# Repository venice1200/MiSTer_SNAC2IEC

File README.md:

# MiSTer_SNAC2IEC
Inspired from the [SNAC Accessory Converter](https://github.com/blue212/SNAC) and the IEC Support of the C64 Core  
I created together with dtimber this little Adapter PCB for the MiSTer FPGA.  
  
The Adapter converts the MiSTer FPGA User Port (Serial IO) into a Commodore IEC/CBM (Serial) Bus Port.    
Use the Adapter to connect a real Commodore Floppy 1541 or compatible devices (SD2IEC/PI1541) to your MiSTer.  
  
I know there are better and faster ways to load a game into a MiSTer's Core, but this is fun 🚀.  
  
### Compatible & Tested Cores  
C64, C128, Commodore Plus/4  
### Tested Hardware  
[SD2IEC](https://www.c64-wiki.com/wiki/SD2IEC), [PI1541](https://cbm-pi1541.firebaseapp.com/), CBM 1541, CBM1541-II, CBM1571, CBM1581 and Printer MPS-803.
  
Cores and some Hardware Devices are also tested with **JiffyDOS** 🚀.  
  
Double check the User Video below.   
  
### Let's go and have fun...
I used "breakout Parts" for the used Voltage-Levelshifter and the Voltage-Regulator as I had them in stock.  
There is also a Full-SMD-Version available, created by dtimber who created the Case as well.  
  
## PCB's
### First Versions  
### Breakout v1.1/SMD v1.0
The first Picture shows the "Breakout Version", the second the "Full-SMD Version".  

### Updated Version(s)  
### Breakout v1.2/SMD 1.1  
Changes:
  * Added support for the SRQ Signal which is needed by the C128 Core for **Fast Serial Mode**.  
    The Breakout Version v1.2 need a second Leveshifter **on Top** of the first one to support the SRQ Signal.  
    Solder two small cables from the Pins LV5 and HV5 to one channel of the second Levelshifter.  
  * Removed 5V support (R1-R4) which needs a Standard SNAC Adapter connected before SNAC2IEC.  
  
The first Picture shows the "Breakout Version", the second the "Full-SMD Version".  

## More Pictures
The Case was designed to look like the C64 Power Supply  

Connector View  
  
Left Connector = IEC/CBM Bus, right Connector = 5V Power from SNAC Port  
                                                     
Soldered PCB Version **with** Level Shifter.  
Use it with the Standard IO Board with SNAC Port and **3.3V** Signal Level.  
  
You need all parts except the "optional's".
  
Soldered PCB Version **without** Level Shifter.  
Only usable with the "first" PCB Versions.  
Use it with SNAC Port's with integrated Level Shifter or with blue212's external SNAC Adapter and **5V** Signal Level.  
  
Just add some 0R 0805 Resistors or a blob of solder to R1,R2,R3 and R4.  

A look inside...  

All Parts for the Breakout-Version  

### BOM Breakout Version  
|Part|Type|
|:---|:---|
|R1-R4|0 ohm 0805 resistors (optional, see schematics)|
|C1|4,7uF 0805 capacitor (optional, see schematics)|
|J1|USB3 type A connector|
|J2|6 pin DIN connector (MAS60)|
|J3|DC barrel connector (optional, 5.5/2.1 mm should be fine for most PSUs)|  
|U1|4-Channel Voltage-Levelshifter (5V/3.3V), add a second ***stacked*** Levelshifter for SRQ|
|U2|5V to 3.3V Voltage Regulator|
  
### BOM Full-SMD-Version v1.0 
|Part|Type|
|:---|:---|
|R1-R4|0 ohm 0805 resistors (optional, see schematics)|
|R5-R12|10k 0805 resistors|
|C1-C3|22nf 0805 capacitors|
|Q1-Q4|N-Channel SOT23 MOSFET transistors (BSS138 or similar)|
|U1|3.3v LM1117 SOT223 regulator|
|J1|USB3 type A connector|
|J2|6 pin DIN connector (MAS60)|
|J3|DC barrel connector (optional, 5.5/2.1 mm should be fine for most PSUs)|  
  
### BOM Full-SMD-Version v1.1 
|Part|Type|
|:---|:---|
|R1-R10|10k 0805 resistors|
|C1-C3|22nf 0805 capacitors|
|Q1-Q5|N-Channel SOT23 MOSFET transistors (BSS138 or similar)|
|U1|3.3v LM1117 SOT223 regulator|
|J1|USB3 type A connector|
|J2|6 pin DIN connector (MAS60)|
|J3|DC barrel connector (optional, 5.5/2.1 mm should be fine for most PSUs)|  
  
### Screws and Brass Nuts  
|Part|Type|
|:---|:---|
|Brass Nuts|M3, outer size 4,6mm, lenght 6mm|
|Screws|M3, Counter Sunk, length 17mm|

### Many Thanks to:
*  [dtimber](https://github.com/dtimber) was helping me with KiCad and he is the Creator of the Case and the **SMD-Version**.
  
### Links:  
*  https://github.com/MiSTer-devel/Main_MiSTer/wiki  
*  https://github.com/MiSTer-devel/Main_MiSTer/wiki/User-Port-(Serial-IO)  
*  https://github.com/MiSTer-devel/C64_MiSTer
*  https://github.com/blue212/SNAC
*  https://misterfpga.org/
*  https://misterfpga.org/viewtopic.php?t=4469
  
### User-Videos:  
* https://youtu.be/zR52L662JqI
* https://www.youtube.com/watch?v=zR52L662JqI
* https://www.youtube.com/watch?v=jKdF6Q4ZU_g
* https://www.youtube.com/watch?v=Q-g8Mt_xXnU
* https://www.youtube.com/watch?v=LXGE7Ap88mE

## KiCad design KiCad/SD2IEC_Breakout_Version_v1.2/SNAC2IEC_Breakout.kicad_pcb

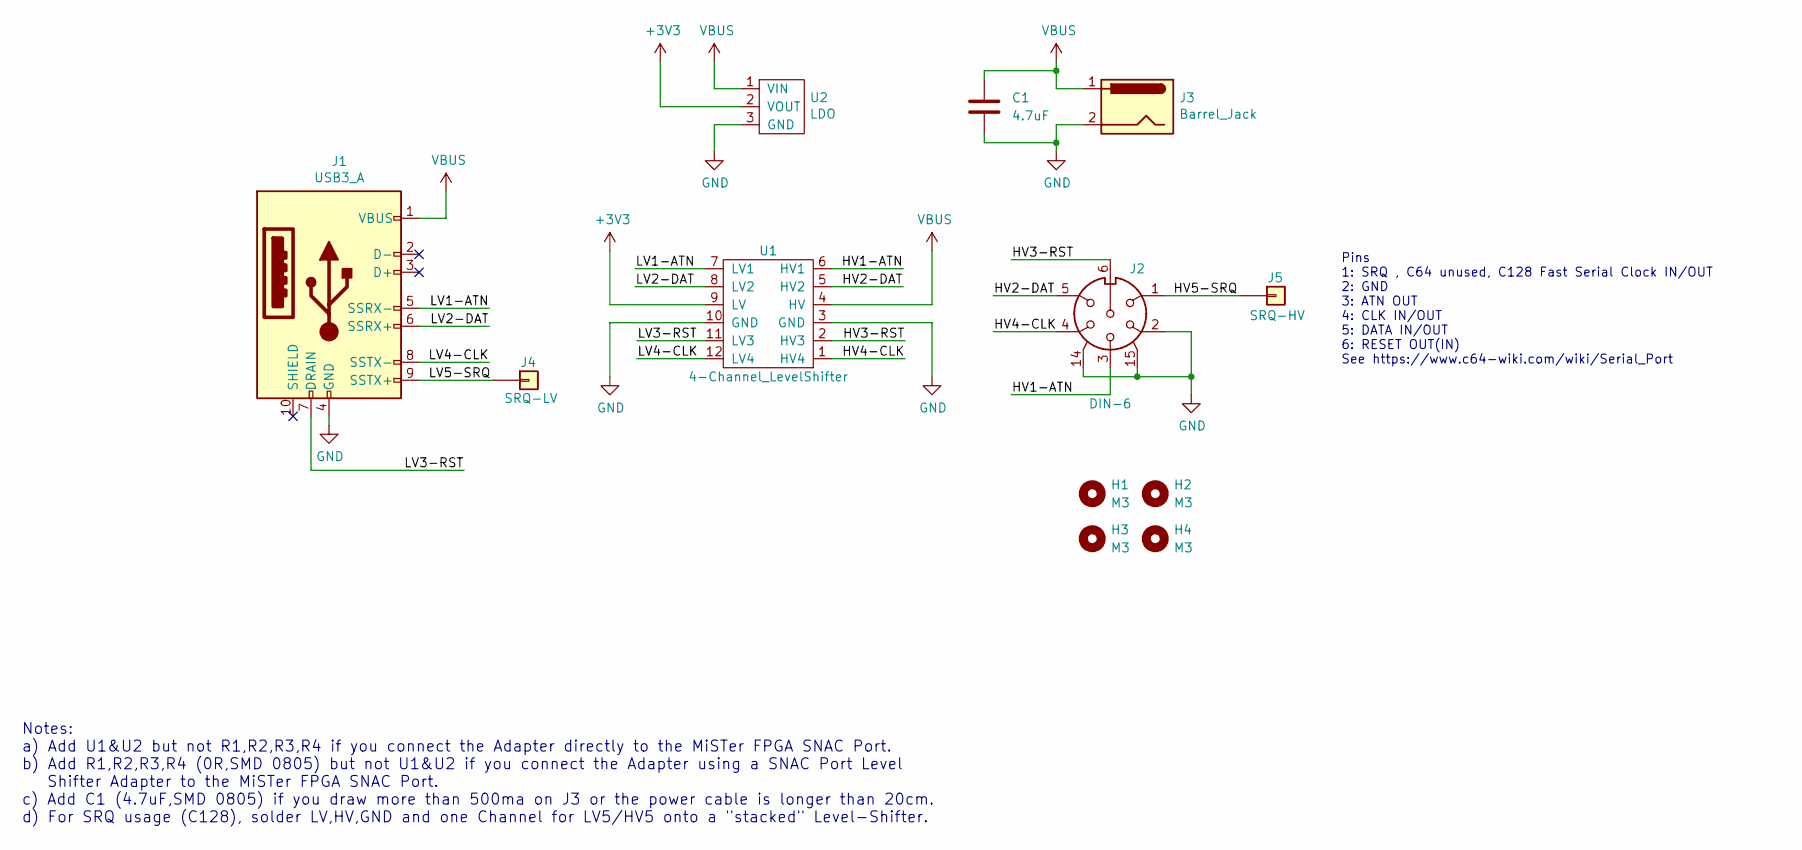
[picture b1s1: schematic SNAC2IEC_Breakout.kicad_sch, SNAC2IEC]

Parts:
C1: 4.7uF; C_0805_2012Metric
H1, H2, H3, H4: M3; MountingHole_3.2mm_M3_ISO7380_Pad
J1: USB3_A; USB3_A_Plug_Wuerth_692112030100_Horizontal
J2: DIN-6; DIN_6Pin_Print_Connector_IEC_Layout
J3: Barrel_Jack; BarrelJack_Wuerth_6941xx301002
J4: SRQ-LV; PinHeader_1x01_P2.54mm_Vertical
J5: SRQ-HV; PinHeader_1x01_P2.54mm_Vertical
U1: 4-Channel_LevelShifter; Breakout_LevelShiffer_4Channel
U2: LDO; Breakout_LDO_AMS1117_3.3V

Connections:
+3V3: U1.9 (LV), U2.2 (VOUT)
/HV1-ATN: J2.3, U1.6 (HV1)
/HV2-DAT: J2.5, U1.5 (HV2)
/HV3-RST: J2.6, U1.2 (HV3)
/HV4-CLK: J2.4, U1.1 (HV4)
/HV5-SRQ: J2.1, J5.1
/LV1-ATN: J1.5 (SSRX-), U1.7 (LV1)
/LV2-DAT: J1.6 (SSRX+), U1.8 (LV2)
/LV3-RST: J1.7 (DRAIN), U1.11 (LV3)
/LV4-CLK: J1.8 (SSTX-), U1.12 (LV4)
/LV5-SRQ: J1.9 (SSTX+), J4.1
GND: C1.2, J1.4 (GND), J2.2, J2.14, J2.15, J3.2, U1.3 (GND), U1.10 (GND), U2.3 (GND)
VBUS: C1.1, J1.1 (VBUS), J3.1, U1.4 (HV), U2.1 (VIN)

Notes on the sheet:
Notes: a) Add U1&U2 but not R1,R2,R3,R4 if you connect the Adapter directly to the MiSTer FPGA SNAC Port. b) Add R1,R2,R3,R4 (0R,SMD 0805) but not U1&U2 if you connect the Adapter using a SNAC Port Level Shifter Adapter to the MiSTer FPGA SNAC Port. c) Add C1 (4.7uF,SMD 0805) if you draw more than 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
Pins 1: SRQ , C64 unused, C128 Fast Serial Clock IN/OUT 2: GND 3: ATN OUT 4: CLK IN/OUT 5: DATA IN/OUT 6: RESET OUT(IN) See https://www.c64-wiki.com/wiki/Serial_Port

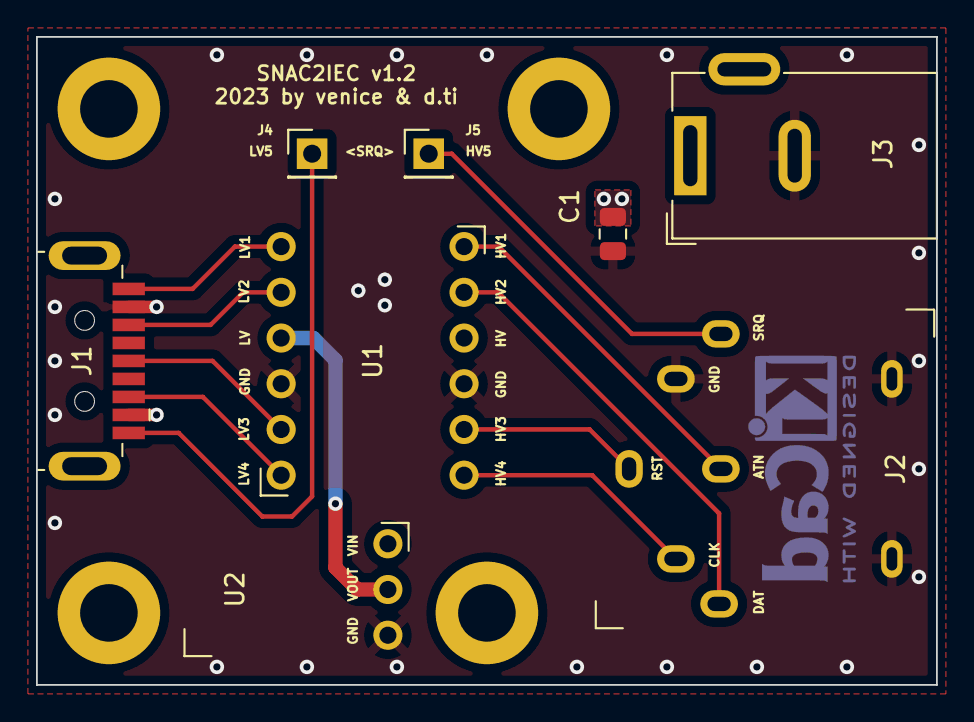
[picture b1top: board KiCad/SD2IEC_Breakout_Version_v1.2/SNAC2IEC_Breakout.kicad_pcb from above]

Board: 2 copper layers, 50.0 x 36.0 mm, 12 parts (0 on the bottom side), 13 nets.

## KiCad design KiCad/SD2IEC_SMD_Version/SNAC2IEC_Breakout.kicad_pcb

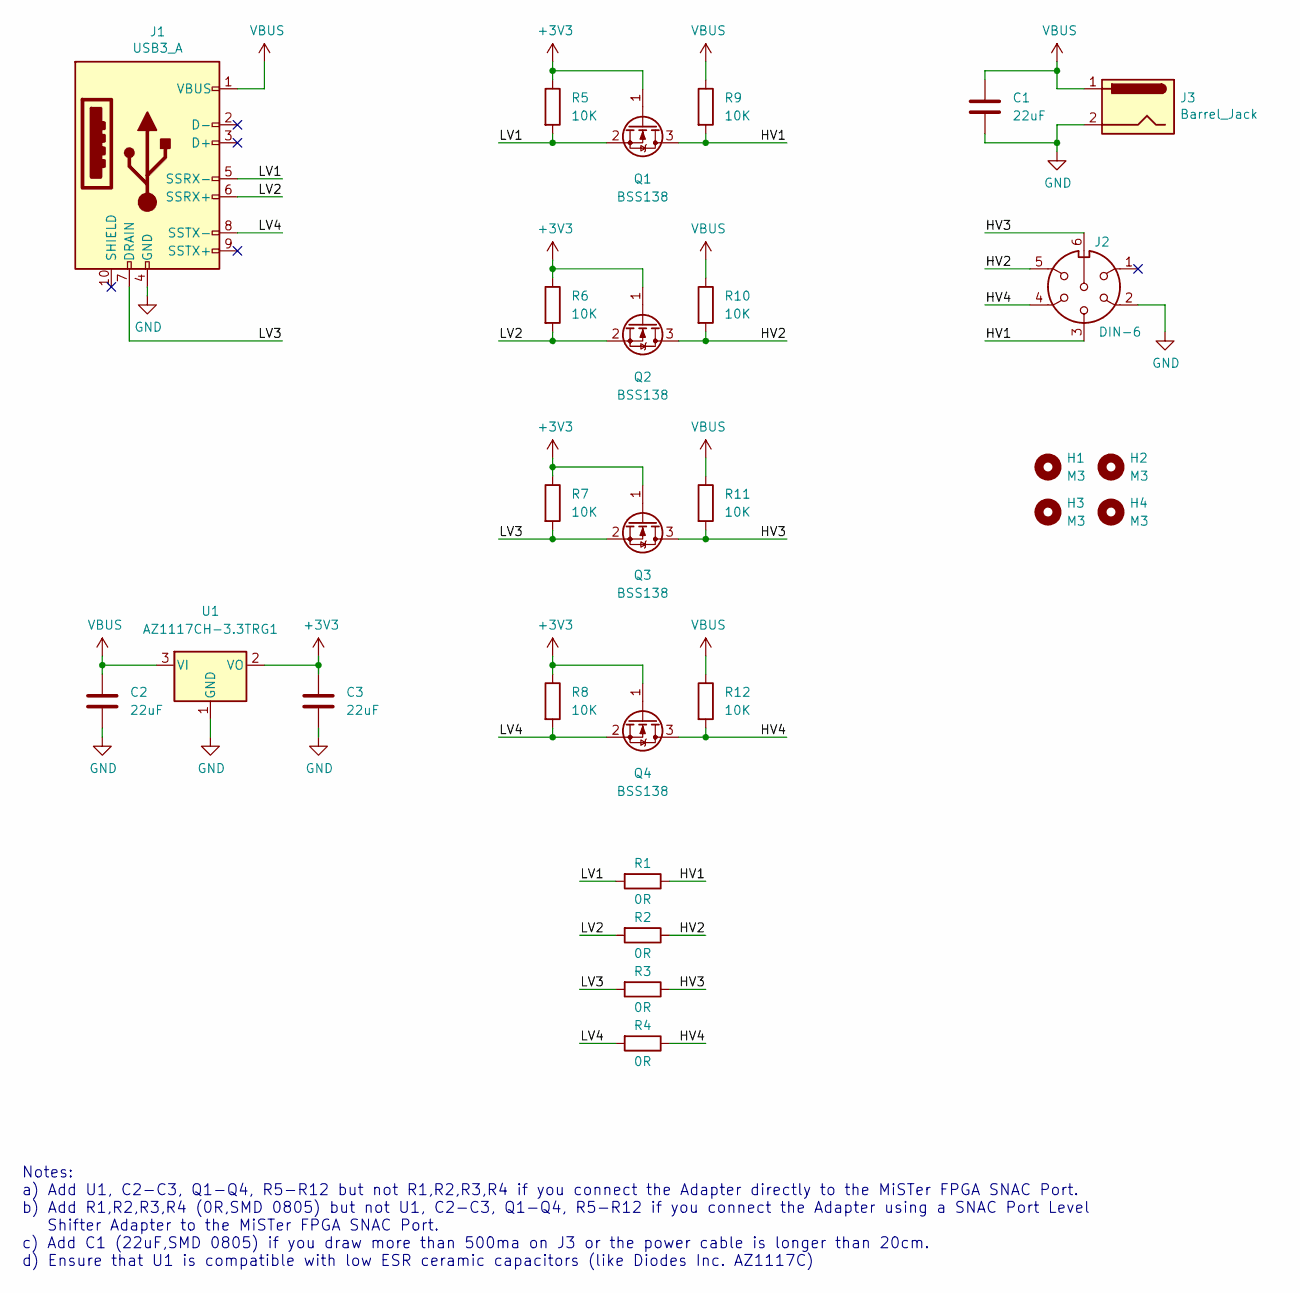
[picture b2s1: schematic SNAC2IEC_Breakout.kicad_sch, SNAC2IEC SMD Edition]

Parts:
C1, C2, C3: 22uF; C_0805_2012Metric
H1, H2, H3, H4: M3; MountingHole_3.2mm_M3_ISO7380_Pad
J1: USB3_A; USB3_A_Plug_Wuerth_692112030100_Horizontal
J2: DIN-6; DIN_6Pin_Print_Connector_IEC_Layout
J3: Barrel_Jack; BarrelJack_Wuerth_6941xx301002
Q1, Q2, Q3, Q4: BSS138; SOT-23
R1, R2, R3, R4: 0R; R_0805_2012Metric_Pad1.20x1.40mm_HandSolder
R5, R6, R7, R8, R9, R10, R11, R12: 10K; R_0805_2012Metric
U1: AZ1117CH-3.3TRG1; SOT-223-3_TabPin2

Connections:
+3V3: C3.1, Q1.1 (G), Q2.1 (G), Q3.1 (G), Q4.1 (G), R5.1, R6.1, R7.1, R8.1, U1.2 (VO)
/HV1: J2.3, Q1.3 (D), R1.1, R9.2
/HV2: J2.5, Q2.3 (D), R2.1, R10.2
/HV3: J2.6, Q3.3 (D), R3.1, R11.2
/HV4: J2.4, Q4.3 (D), R4.1, R12.2
/LV1: J1.5 (SSRX-), Q1.2 (S), R1.2, R5.2
/LV2: J1.6 (SSRX+), Q2.2 (S), R2.2, R6.2
/LV3: J1.7 (DRAIN), Q3.2 (S), R3.2, R7.2
/LV4: J1.8 (SSTX-), Q4.2 (S), R4.2, R8.2
GND: C1.2, C2.2, C3.2, J1.4 (GND), J2.2, J3.2, U1.1 (GND)
VBUS: C1.1, C2.1, J1.1 (VBUS), J3.1, R9.1, R10.1, R11.1, R12.1, U1.3 (VI)

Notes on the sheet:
Notes: a) Add U1, C2-C3, Q1-Q4, R5-R12 but not R1,R2,R3,R4 if you connect the Adapter directly to the MiSTer FPGA SNAC Port. b) Add R1,R2,R3,R4 (0R,SMD 0805) but not U1, C2-C3, Q1-Q4, R5-R12 if you connect the Adapter using a SNAC Port Level Shifter Adapter to the MiSTer FPGA SNAC Port. c) Add C1 (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

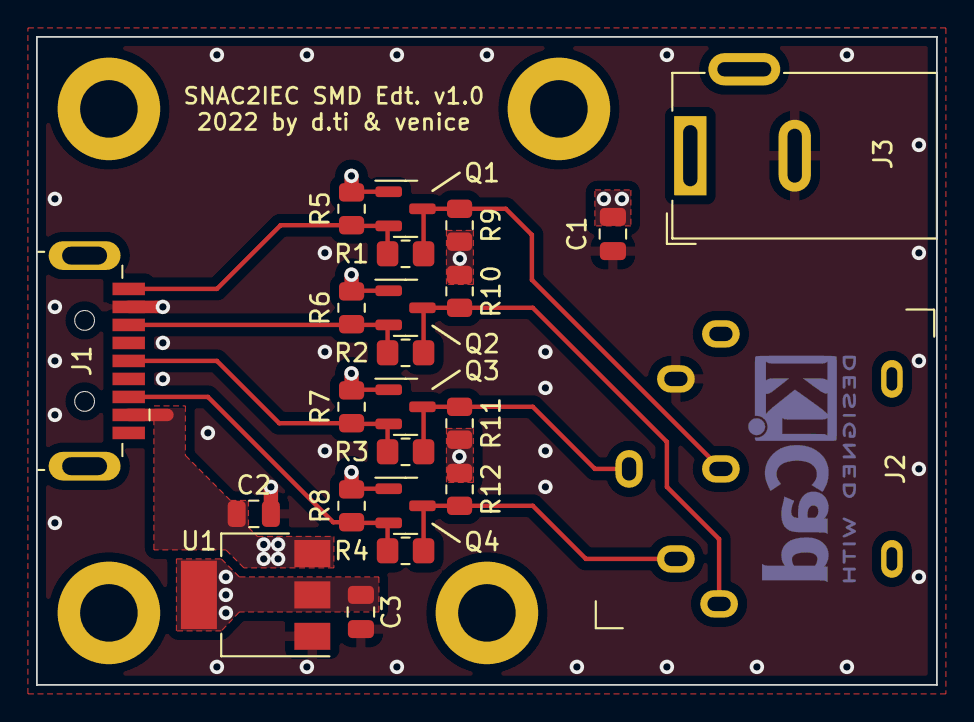
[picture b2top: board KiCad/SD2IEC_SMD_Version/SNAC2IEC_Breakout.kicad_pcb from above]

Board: 2 copper layers, 50.0 x 36.0 mm, 27 parts (0 on the bottom side), 11 nets.

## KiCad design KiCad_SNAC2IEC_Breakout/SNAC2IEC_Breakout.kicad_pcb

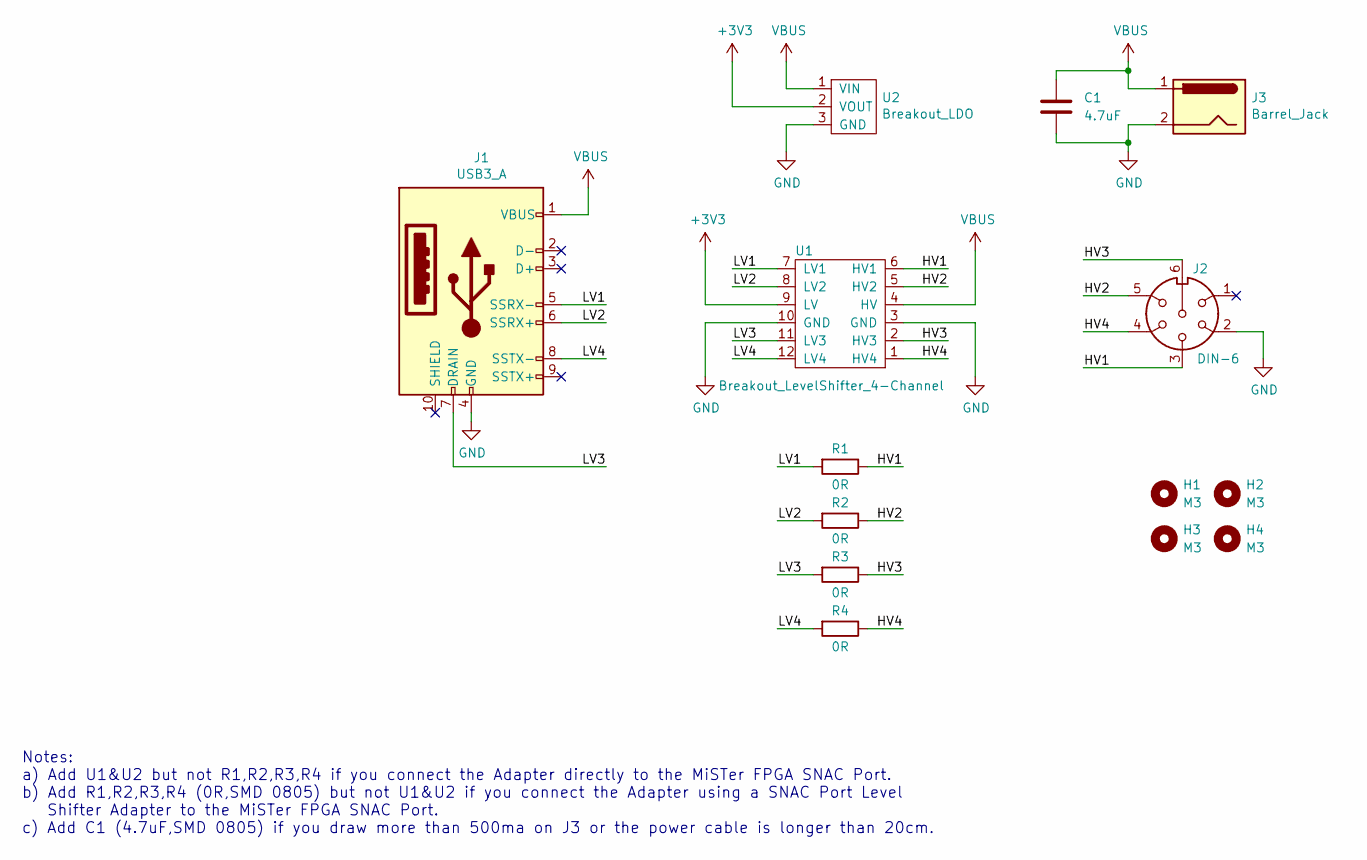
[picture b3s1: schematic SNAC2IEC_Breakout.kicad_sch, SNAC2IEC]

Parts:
C1: 4.7uF; C_0805_2012Metric
H1, H2, H3, H4: M3; MountingHole_3.2mm_M3_ISO7380_Pad
J1: USB3_A; USB3_A_Plug_Wuerth_692112030100_Horizontal
J2: DIN-6; DIN_6Pin_Print_Connector_IEC_Layout
J3: Barrel_Jack; BarrelJack_Wuerth_6941xx301002
R1, R2, R3, R4: 0R; R_0805_2012Metric_Pad1.20x1.40mm_HandSolder
U1: Breakout_LevelShifter_4-Channel; Breakout_LevelShiffer_4Channel
U2: Breakout_LDO; Breakout_LDO_AMS1117_3.3V

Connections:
+3V3: U1.9 (LV), U2.2 (VOUT)
/HV1: J2.3, R1.1, U1.6 (HV1)
/HV2: J2.5, R2.1, U1.5 (HV2)
/HV3: J2.6, R3.1, U1.2 (HV3)
/HV4: J2.4, R4.1, U1.1 (HV4)
/LV1: J1.5 (SSRX-), R1.2, U1.7 (LV1)
/LV2: J1.6 (SSRX+), R2.2, U1.8 (LV2)
/LV3: J1.7 (DRAIN), R3.2, U1.11 (LV3)
/LV4: J1.8 (SSTX-), R4.2, U1.12 (LV4)
GND: C1.2, J1.4 (GND), J2.2, J3.2, U1.3 (GND), U1.10 (GND), U2.3 (GND)
VBUS: C1.1, J1.1 (VBUS), J3.1, U1.4 (HV), U2.1 (VIN)

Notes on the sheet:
Notes: a) Add U1&U2 but not R1,R2,R3,R4 if you connect the Adapter directly to the MiSTer FPGA SNAC Port. b) Add R1,R2,R3,R4 (0R,SMD 0805) but not U1&U2 if you connect the Adapter using a SNAC Port Level Shifter Adapter to the MiSTer FPGA SNAC Port. c) Add C1 (4.7uF,SMD 0805) if you draw more than 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

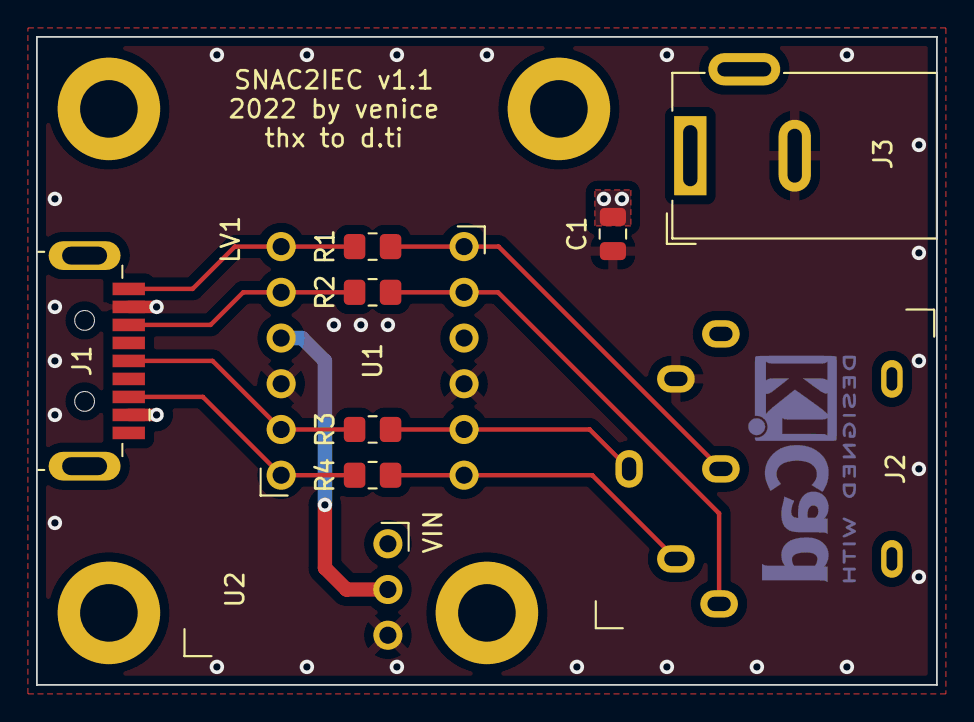
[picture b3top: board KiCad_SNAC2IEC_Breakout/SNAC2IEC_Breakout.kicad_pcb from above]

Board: 2 copper layers, 50.0 x 36.0 mm, 14 parts (0 on the bottom side), 11 nets.

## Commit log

2022-04-04 Add Pictures
2022-04-04 Add Case Picture
2022-04-06 Updated Pics
2022-04-06 Updates Files
2022-04-06 New Pics
2022-04-06 Add 3D Files
2022-04-06 Adding KiCad & Gerber
2022-04-07 New 3D Files
2022-04-12 Added BOMs
2023-02-28 Update Breakout Version to v1.2
    Use a stack of Levelshifter
2023-02-28 Dokumentation/Pictures for SRQ Support
2023-03-06 New SMD v1.1
    Including SRQ Support
2023-04-01 Adding MPS-803
2023-04-01 BOM SMD v1.1

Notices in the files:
README.md:
License: GPL v3
